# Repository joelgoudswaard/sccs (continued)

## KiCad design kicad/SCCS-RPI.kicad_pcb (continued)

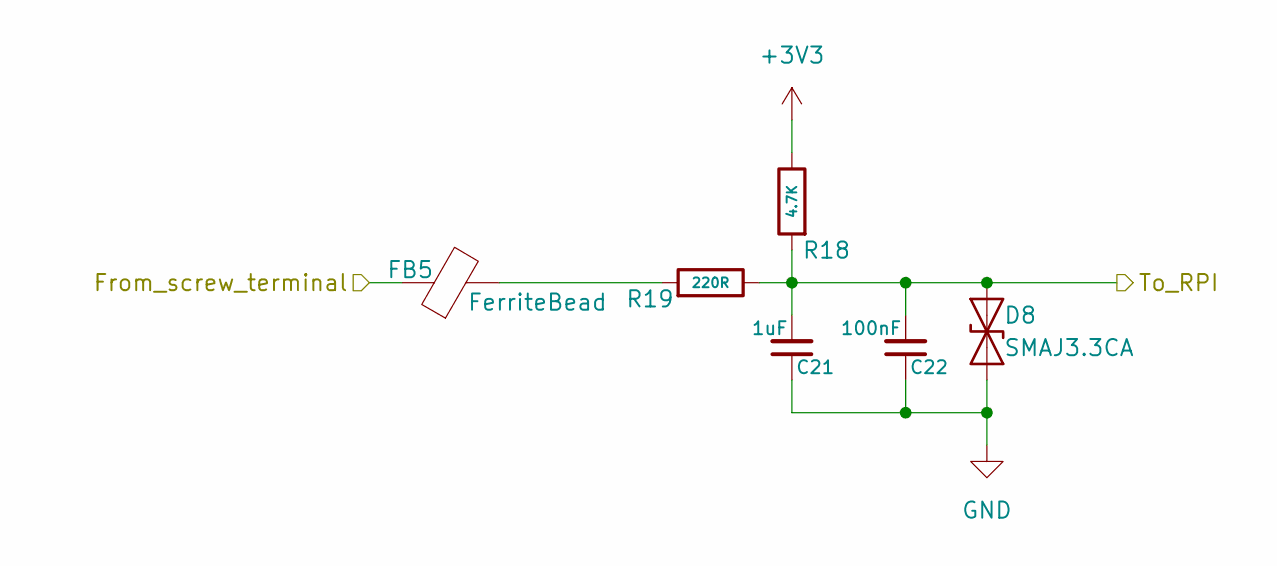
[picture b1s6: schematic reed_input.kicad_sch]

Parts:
C21: 1uF; C_0805_2012Metric; LCSC Part # C91185
C22: 100nF; C_0805_2012Metric; LCSC Part # C49678
D8: SMAJ3.3CA; D_SMA; LCSC Part # C18199545
FB5: FerriteBead; L_0603_1608Metric; LCSC Part # C1002
R18: 4.7K; R_0805_2012Metric; LCSC Part # C17673
R19: 220R; R_0805_2012Metric; LCSC Part # C17557

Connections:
+3V3: R18.1; also elsewhere on the board
/Reed1_input: C21.2, C22.2, D8.2 (A2), R18.2, R19.1; also elsewhere on the board
/Reed Switch 1/From_screw_terminal: FB5.1; also elsewhere on the board
GND: C21.1, C22.1, D8.1 (A1); also elsewhere on the board
unnamed: FB5.2, R19.2

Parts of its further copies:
C23, C25, C27, C29, C31, C33, C35: 1uF; C_0805_2012Metric; LCSC Part # C91185
C24, C26, C28, C30, C32, C34, C36: 100nF; C_0805_2012Metric; LCSC Part # C49678
D9, D10, D11, D12, D13, D14, D15: SMAJ3.3CA; D_SMA; LCSC Part # C18199545
FB6, FB7, FB8, FB9, FB10, FB11, FB12: FerriteBead; L_0603_1608Metric; LCSC Part # C1002
R20, R22, R24, R26, R28, R30, R32: 4.7K; R_0805_2012Metric; LCSC Part # C17673
R21, R23, R25, R27, R29, R31, R33: 220R; R_0805_2012Metric; LCSC Part # C17557

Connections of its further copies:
+3V3: R20.1, R22.1, R24.1, R26.1, R28.1, R30.1, R32.1; also elsewhere on the board
/Reed2_input: C23.2, C24.2, D9.2 (A2), R20.2, R21.1; also elsewhere on the board
/Reed3_input: C25.2, C26.2, D10.2 (A2), R22.2, R23.1; also elsewhere on the board
/Reed4_input: C27.2, C28.2, D11.2 (A2), R24.2, R25.1; also elsewhere on the board
/Reed5_input: C29.2, C30.2, D12.2 (A2), R26.2, R27.1; also elsewhere on the board
/Reed6_input: C31.2, C32.2, D13.2 (A2), R28.2, R29.1; also elsewhere on the board
/Reed7_input: C33.2, C34.2, D14.2 (A2), R30.2, R31.1; also elsewhere on the board
/Reed8_input: C35.2, C36.2, D15.2 (A2), R32.2, R33.1; also elsewhere on the board
/Reed Switch 2/From_screw_terminal: FB6.1; also elsewhere on the board
/Reed Switch 3/From_screw_terminal: FB7.1; also elsewhere on the board
/Reed Switch 4/From_screw_terminal: FB8.1; also elsewhere on the board
/Reed Switch 5/From_screw_terminal: FB9.1; also elsewhere on the board
/Reed Switch 6/From_screw_terminal: FB10.1; also elsewhere on the board
/Reed Switch 7/From_screw_terminal: FB11.1; also elsewhere on the board
/Reed Switch 8/From_screw_terminal: FB12.1; also elsewhere on the board
GND: C23.1, C24.1, C25.1, C26.1, C27.1, C28.1, C29.1, C30.1, C31.1, C32.1, C33.1, C34.1, C35.1, C36.1, D9.1 (A1), D10.1 (A1), D11.1 (A1), D12.1 (A1), D13.1 (A1), D14.1 (A1), D15.1 (A1); also elsewhere on the board
unnamed: FB6.2, R21.2
unnamed: FB7.2, R23.2
unnamed: FB8.2, R25.2
unnamed: FB9.2, R27.2
unnamed: FB10.2, R29.2
unnamed: FB11.2, R31.2
unnamed: FB12.2, R33.2

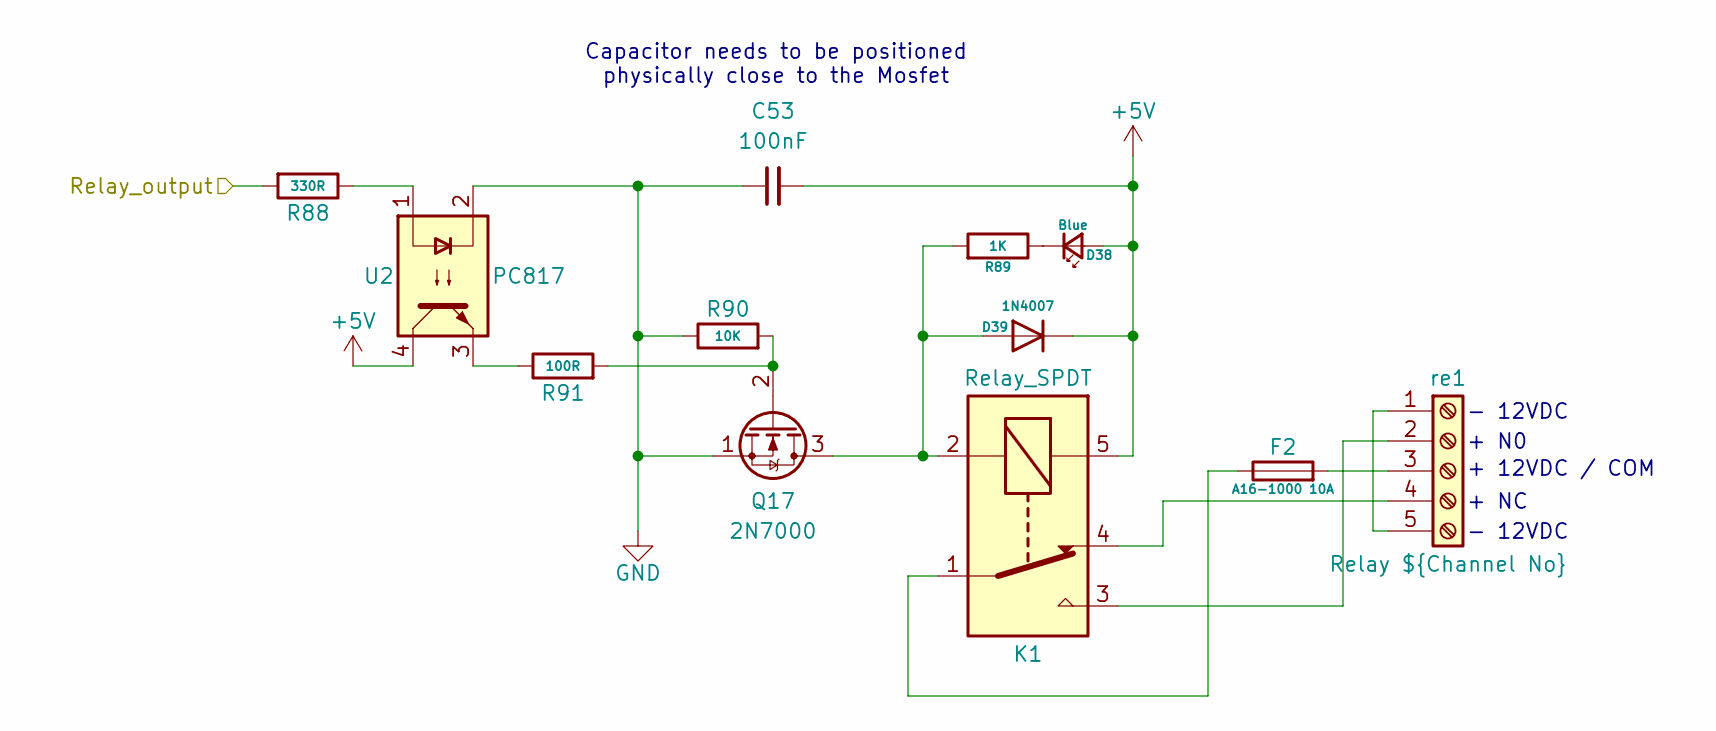
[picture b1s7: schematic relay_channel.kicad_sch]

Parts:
C53: 100nF; C_0805_2012Metric; LCSC Part # C49678
D38: Blue; LED_0603_1608Metric; LCSC Part # C2288
D39: 1N4007; D_SMA; LCSC Part # C64915
F2: A16-1000 10A; Fuse_Bourns_MF-RG1000; LCSC Part # C135398
K1: Relay_SPDT; Relay_SPDT_SANYOU_SRD_Series_Form_C; LCSC Part # C35449
Q17: 2N7000; TO-92_Inline; LCSC Part # C9114
R88: 330R; R_0805_2012Metric; LCSC Part # C17630
R89: 1K; R_0603_1608Metric; LCSC Part # C5123612
R90: 10K; R_0805_2012Metric; LCSC Part # C17414
R91: 100R; R_0805_2012Metric; LCSC Part # C17408
U2: PC817; DIP-4_W7.62mm; LCSC Part # C5353
re1: Relay ${Channel No}; TerminalBlock_Phoenix_MKDS-3-5-5.08_1x05_P5.08mm_Horizontal; LCSC Part # C8423

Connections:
+5V: C53.2, D38.2 (A), D39.1 (K), K1.5, U2.4; also elsewhere on the board
/Relay1_output: R88.2; also elsewhere on the board
GND: C53.1, Q17.1 (S), R90.1, U2.2; also elsewhere on the board
unnamed: D38.1 (K), R89.1
unnamed: D39.2 (A), K1.2, Q17.3 (D), R89.2
unnamed: F2.1, K1.1
unnamed: Q17.2 (G), R90.2, R91.2
unnamed: R88.1, U2.1
unnamed: R91.1, U2.3
unnamed: re1.1, re1.5
unnamed: K1.3, re1.2
unnamed: F2.2, re1.3
unnamed: K1.4, re1.4

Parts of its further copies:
C54, C55, C56: 100nF; C_0805_2012Metric; LCSC Part # C49678
D40, D42, D44: Blue; LED_0603_1608Metric; LCSC Part # C2288
D41, D43, D45: 1N4007; D_SMA; LCSC Part # C64915
F3, F4, F5: A16-1000 10A; Fuse_Bourns_MF-RG1000; LCSC Part # C135398
K2, K3, K4: Relay_SPDT; Relay_SPDT_SANYOU_SRD_Series_Form_C; LCSC Part # C35449
Q18, Q19, Q20: 2N7000; TO-92_Inline; LCSC Part # C9114
R92, R96, R100: 330R; R_0805_2012Metric; LCSC Part # C17630
R93, R97, R101: 1K; R_0603_1608Metric; LCSC Part # C5123612
R94, R98, R102: 10K; R_0805_2012Metric; LCSC Part # C17414
R95, R99, R103: 100R; R_0805_2012Metric; LCSC Part # C17408
U3, U4, U5: PC817; DIP-4_W7.62mm; LCSC Part # C5353

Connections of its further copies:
+5V: C54.2, C55.2, C56.2, D40.2 (A), D41.1 (K), D42.2 (A), D43.1 (K), D44.2 (A), D45.1 (K), K2.5, K3.5, K4.5, U3.4, U4.4, U5.4; also elsewhere on the board
/Relay2_output: R92.2; also elsewhere on the board
/Relay3_output: R96.2; also elsewhere on the board
/Relay4_output: R100.2; also elsewhere on the board
GND: C54.1, C55.1, C56.1, Q18.1 (S), Q19.1 (S), Q20.1 (S), R94.1, R98.1, R102.1, U3.2, U4.2, U5.2; also elsewhere on the board
unnamed: D40.1 (K), R93.1
unnamed: D41.2 (A), K2.2, Q18.3 (D), R93.2
unnamed: D42.1 (K), R97.1
unnamed: D43.2 (A), K3.2, Q19.3 (D), R97.2
unnamed: D44.1 (K), R101.1
unnamed: D45.2 (A), K4.2, Q20.3 (D), R101.2
unnamed: F3.1, K2.1
unnamed: F4.1, K3.1
unnamed: F5.1, K4.1
unnamed: Q18.2 (G), R94.2, R95.2
unnamed: Q19.2 (G), R98.2, R99.2
unnamed: Q20.2 (G), R102.2, R103.2
unnamed: R92.1, U3.1
unnamed: R95.1, U3.3
unnamed: R96.1, U4.1
unnamed: R99.1, U4.3
unnamed: R100.1, U5.1
unnamed: R103.1, U5.3
unnamed 189: K2.3; also elsewhere on the board
unnamed 190: F3.2; also elsewhere on the board
unnamed 191: K2.4; also elsewhere on the board
unnamed 193: K3.3; also elsewhere on the board
unnamed 194: F4.2; also elsewhere on the board
unnamed 195: K3.4; also elsewhere on the board
unnamed 197: K4.3; also elsewhere on the board
unnamed 198: F5.2; also elsewhere on the board
unnamed 199: K4.4; also elsewhere on the board

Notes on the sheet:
+ NC
+ N0
+ 12VDC / COM
- 12VDC
Capacitor needs to be positioned physically close to the Mosfet

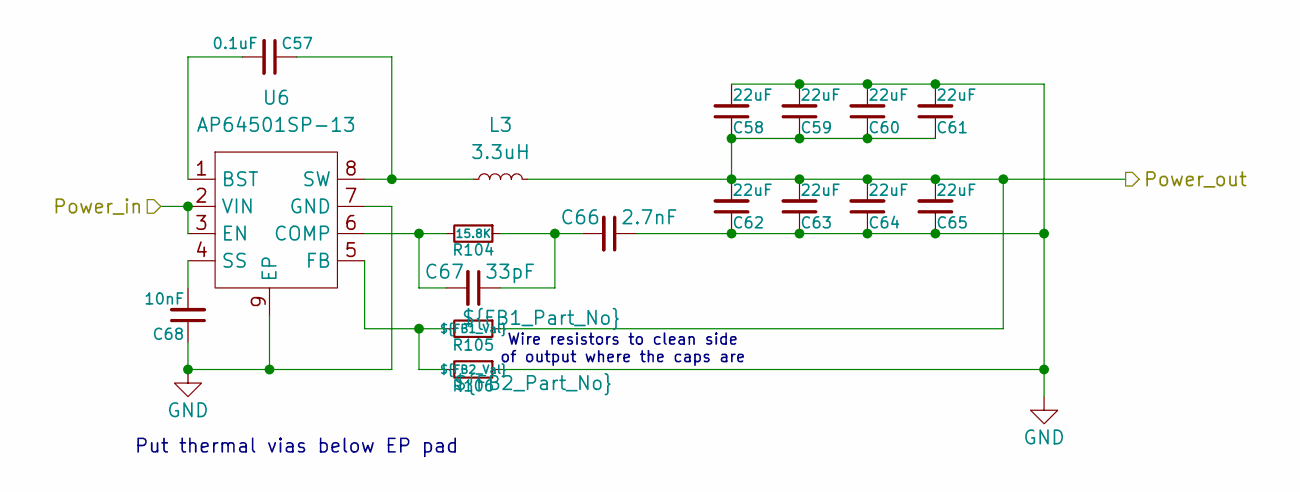
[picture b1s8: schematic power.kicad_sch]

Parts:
C57: 0.1uF; C_0805_2012Metric; LCSC Part # C86041
C58, C59, C60, C61, C62, C63, C64, C65: 22uF; C_0805_2012Metric; LCSC Part # C86816
C66: 2.7nF; C_0805_2012Metric; LCSC Part # C113859
C67: 33pF; C_0805_2012Metric; LCSC Part # C541516
C68: 10nF; C_0805_2012Metric; LCSC Part # C237168
L3: 3.3uH; L_SXN_SMDRI127; LCSC Part # C24550
R104: 15.8K; R_0805_2012Metric; LCSC Part # C17468
R105: ${FB1_Val}; R_0805_2012Metric; LCSC Part # ${FB1_Part_No}
R106: ${FB2_Val}; R_0805_2012Metric; LCSC Part # ${FB2_Part_No}
U6: AP64501SP-13; SOIC-8-1EP_3.9x4.9mm_P1.27mm_EP2.95x4.9mm_Mask2.71x3.4mm_Th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; LCSC Part # C2071517

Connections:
+5V: C58.1, C59.1, C60.1, C61.1, C62.2, C63.2, C64.2, C65.2, L3.2, R105.1; also elsewhere on the board
/Power - 3V3/Power_in: U6.2 (VIN), U6.3 (EN); also elsewhere on the board
GND: C58.2, C59.2, C60.2, C61.2, C62.1, C63.1, C64.1, C65.1, C66.1, C68.1, R106.1, U6.7 (GND), U6.9 (EP); also elsewhere on the board
unnamed: C66.2, C67.1, R104.1
unnamed: C57.2, U6.1 (BST)
unnamed: C67.2, R104.2, U6.6 (COMP)
unnamed: R105.2, R106.2, U6.5 (FB)
unnamed: C68.2, U6.4 (SS)
unnamed: C57.1, L3.1, U6.8 (SW)

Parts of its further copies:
C69: 0.1uF; C_0805_2012Metric; LCSC Part # C86041
C70, C71, C72, C73, C74, C75, C76, C77: 22uF; C_0805_2012Metric; LCSC Part # C86816
C78: 2.7nF; C_0805_2012Metric; LCSC Part # C113859
C79: 33pF; C_0805_2012Metric; LCSC Part # C541516
C80: 10nF; C_0805_2012Metric; LCSC Part # C237168
L4: 3.3uH; L_SXN_SMDRI127; LCSC Part # C24550
R107: 15.8K; R_0805_2012Metric; LCSC Part # C17468
U7: AP64501SP-13; SOIC-8-1EP_3.9x4.9mm_P1.27mm_EP2.95x4.9mm_Mask2.71x3.4mm_Th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; LCSC Part # C2071517

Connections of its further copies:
+3V3: C70.1, C71.1, C72.1, C73.1, C74.2, C75.2, C76.2, C77.2, L4.2; also elsewhere on the board
/Power - 3V3/Power_in: U7.2 (VIN), U7.3 (EN); also elsewhere on the board
GND: C70.2, C71.2, C72.2, C73.2, C74.1, C75.1, C76.1, C77.1, C78.1, C80.1, U7.7 (GND), U7.9 (EP); also elsewhere on the board
unnamed: C78.2, C79.1, R107.1
unnamed: C69.2, U7.1 (BST)
unnamed: C79.2, R107.2, U7.6 (COMP)
unnamed 177: U7.5 (FB); also elsewhere on the board
unnamed: C80.2, U7.4 (SS)
unnamed: C69.1, L4.1, U7.8 (SW)

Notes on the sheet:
Put thermal vias below EP pad
Wire resistors to clean side of output where the caps are

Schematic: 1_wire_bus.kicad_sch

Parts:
C17: 100nF; C_0805_2012Metric; LCSC Part # C49678
D7: SMAJ3.3CA; D_SMA; LCSC Part # C18199545
FB1: FerriteBead; L_0603_1608Metric; LCSC Part # C1002
R14: 2.2K; R_0805_2012Metric; LCSC Part # C17520
i3: Temp Sensors; TerminalBlock_Phoenix_MKDS-1,5-3-5.08_1x03_P5.08mm_Horizont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; LCSC Part # C8412

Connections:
+3V3: C17.1, R14.2, i3.1; also elsewhere on the board
/Temp1_sensor_input: D7.2 (A2), FB1.2, R14.1; also elsewhere on the board
GND: C17.2, D7.1 (A1), i3.3; also elsewhere on the board
unnamed: FB1.1, i3.2

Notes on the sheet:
Yellow/Data
Red/+
Black/-

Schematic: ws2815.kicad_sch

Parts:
D36: SMAJ5.0CA; D_SMA; LCSC Part # C78402
R86: 33R; R_0805_2012Metric; LCSC Part # C17634

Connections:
/WS281X Channel 1/WS281X_In: R86.1; also elsewhere on the board
/WS281X Channel 1/WS281X_Out: D36.2 (A2), R86.2; also elsewhere on the board
GND: D36.1 (A1); also elsewhere on the board

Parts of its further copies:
D37: SMAJ5.0CA; D_SMA; LCSC Part # C78402
R87: 33R; R_0805_2012Metric; LCSC Part # C17634

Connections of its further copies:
/WS281X Channel 2/WS281X_In: R87.1; also elsewhere on the board
/WS281X Channel 2/WS281X_Out: D37.2 (A2), R87.2; also elsewhere on the board
GND: D37.1 (A1); also elsewhere on the board

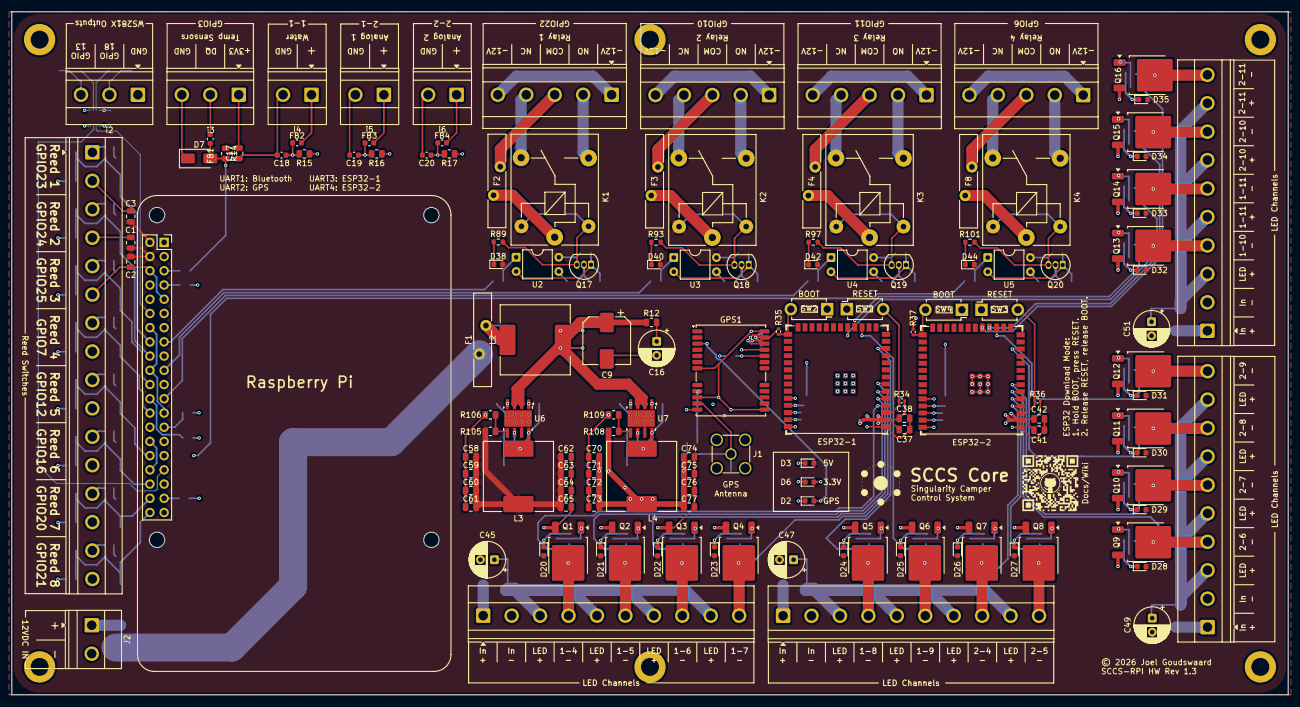
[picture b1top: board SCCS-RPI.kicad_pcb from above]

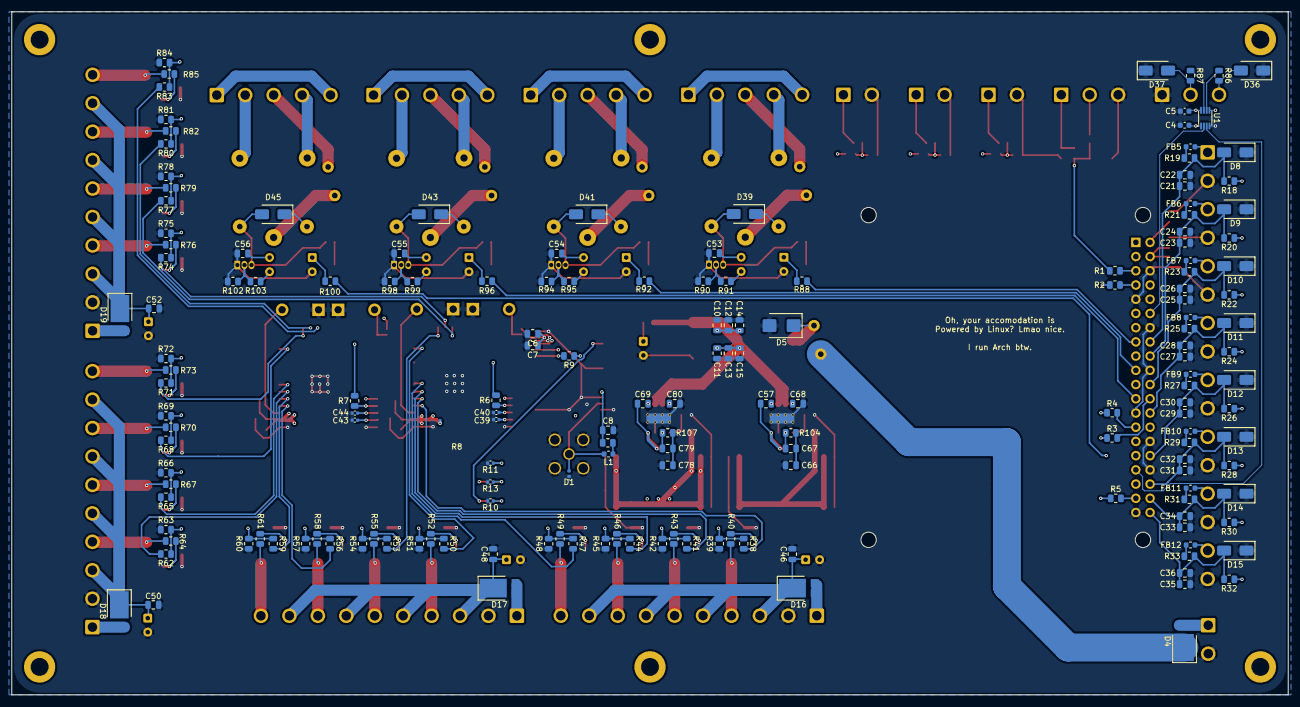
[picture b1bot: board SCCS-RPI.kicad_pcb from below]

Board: 4 copper layers, 228.0 x 122.0 mm, 311 parts (170 on the bottom side), 200 nets.

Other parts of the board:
D17, D18, D19: D_PowerDI-5
D21, D29: Red; LED_0603_1608Metric
D22, D30: Green; LED_0603_1608Metric
D23, D24, D25, D26, D27, D28, D31, D32, D33, D34, D35: White; LED_0603_1608Metric
R108: 100K; R_0805_2012Metric
R109: 32.4K; R_0805_2012Metric
RP?: Raspberry_Pi_2_3; raspberrypi_4
i5: Analog 1; TerminalBlock_Phoenix_MKDS-1,5-2-5.08_1x02_P5.08mm_Horizont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
i6: Analog 2; TerminalBlock_Phoenix_MKDS-1,5-2-5.08_1x02_P5.08mm_Horizont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
re2: Relay 2; TerminalBlock_Phoenix_MKDS-3-5-5.08_1x05_P5.08mm_Horizontal
re3: Relay 3; TerminalBlock_Phoenix_MKDS-3-5-5.08_1x05_P5.08mm_Horizontal
re4: Relay 4; TerminalBlock_Phoenix_MKDS-3-5-5.08_1x05_P5.08mm_Horizontal

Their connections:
+3V3: R108.1; also elsewhere on the board
+5V: D21.2 (A), D22.2 (A), D23.2 (A), D24.2 (A), D25.2 (A), D26.2 (A), D27.2 (A), D28.2 (A), D29.2 (A), D30.2 (A), D31.2 (A), D32.2 (A), D33.2 (A), D34.2 (A), D35.2 (A); also elsewhere on the board
/LED Power 2/12vdc_in: D17.2 (A); also elsewhere on the board
/LED Power 2/12vdc_out: D17.1 (K); also elsewhere on the board
/LED Power 3/12vdc_in: D18.2 (A); also elsewhere on the board
/LED Power 3/12vdc_out: D18.1 (K); also elsewhere on the board
/LED Power 4/12vdc_in: D19.2 (A); also elsewhere on the board
/LED Power 4/12vdc_out: D19.1 (K); also elsewhere on the board
GND: R109.1, i5.2, i6.2; also elsewhere on the board
unnamed 95: D21.1 (K); also elsewhere on the board
unnamed 96: D22.1 (K); also elsewhere on the board
unnamed 97: D23.1 (K); also elsewhere on the board
unnamed 98: D24.1 (K); also elsewhere on the board
unnamed 99: D25.1 (K); also elsewhere on the board
unnamed 100: D26.1 (K); also elsewhere on the board
unnamed 101: D27.1 (K); also elsewhere on the board
unnamed 102: D28.1 (K); also elsewhere on the board
unnamed 103: D29.1 (K); also elsewhere on the board
unnamed 104: D30.1 (K); also elsewhere on the board
unnamed 105: D31.1 (K); also elsewhere on the board
unnamed 106: D32.1 (K); also elsewhere on the board
unnamed 107: D33.1 (K); also elsewhere on the board
unnamed 108: D34.1 (K); also elsewhere on the board
unnamed 109: D35.1 (K); also elsewhere on the board
unnamed 177: R108.2, R109.2; also elsewhere on the board
unnamed 182: i5.1; also elsewhere on the board
unnamed 183: i6.1; also elsewhere on the board
unnamed: re2.1, re2.5
unnamed 189: re2.2; also elsewhere on the board
unnamed 190: re2.3; also elsewhere on the board
unnamed 191: re2.4; also elsewhere on the board
unnamed: re3.1, re3.5
unnamed 193: re3.2; also elsewhere on the board
unnamed 194: re3.3; also elsewhere on the board
unnamed 195: re3.4; also elsewhere on the board
unnamed: re4.1, re4.5
unnamed 197: re4.2; also elsewhere on the board
unnamed 198: re4.3; also elsewhere on the board
unnamed 199: re4.4; also elsewhere on the board

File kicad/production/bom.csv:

Designator,Footprint,Quantity,Value,LCSC Part #
"C1, C10",0805,2,10uF,C15850
"C11, C17, C2, C22, C24, C26, C28, C30, C32, C34, C36, C46, C48, C50, C52, C53, C54, C55, C56, C8",0805,20,100nF,C49678
"C12, C13, C14, C15, C3, C37, C41, C58, C59, C6, C60, C61, C62, C63, C64, C65, C70, C71, C72, C73, C74, C75, C76, C77",0805,24,22uF,C86816
"C16, C45, C47, C49, C51",CP_Radial_D6.3mm_P2.50mm,5,100uF,C44587
"C18, C19, C20, C4, C5",0603,5,100nF,C1590
"C21, C23, C25, C27, C29, C31, C33, C35",0805,8,1uF,C91185
"C38, C42, C57, C69, C7",0805,5,0.1uF,C86041
"C39, C40, C43, C44",0402,4,100nF,C60474
"C66, C78",0805,2,2.7nF,C113859
"C67, C79",0805,2,33pF,C541516
"C68, C80",0805,2,10nF,C237168
C9,CP_Elec_8x10,1,220uF,C165536
D1,0402,1,ESD103-B1-02EL,C535146
"D10, D11, D12, D13, D14, D15, D7, D8, D9",D_SMA,9,SMAJ3.3CA,C18199545
"D16, D17, D18, D19, D4",D_PowerDI-5,5,~,C2759901
D2,0603,1,GPS,C2286
"D20, D23, D24, D25, D26, D27, D28, D31, D32, D33, D34, D35",0603,12,White,C2290
"D21, D29",0603,2,Red,C2286
"D22, D30",0603,2,Green,C12065
D3,0603,1,5V,C2286
"D36, D37",D_SMA,2,SMAJ5.0CA,C78402
"D38, D40, D42, D44",0603,4,Blue,C2288
"D39, D41, D43, D45",D_SMA,4,1N4007,C64915
D5,D_SMB,1,SMAJ18A/TR13,C571369
D6,0603,1,3.3V,C2286
"ESP32-1, ESP32-2",ESP32-S3-WROOM-1U,2,ESP32-S3-WROOM-1,C3013946
"F1, F2, F3, F4, F5",Fuse_Bourns_MF-RG1000,5,A16-1000 10A,C135398
"FB1, FB10, FB11, FB12, FB2, FB3, FB4, FB5, FB6, FB7, FB8, FB9",0603,12,FerriteBead,C1002
GPS1,ublox_NEO,1,NEO-M9N-00B,C5119087
I1,"TerminalBlock_Phoenix_MKDS-1,5-16-5.08_1x16_P5.08mm_Horizontal",1,Reed Switches,C508906
I2,"TerminalBlock_Phoenix_MKDS-1,5-3-5.08_1x03_P5.08mm_Horizontal",1,WS281X Outputs,C8412
I3,"TerminalBlock_Phoenix_MKDS-1,5-3-5.08_1x03_P5.08mm_Horizontal",1,Temp Sensors,C8412
I4,"TerminalBlock_Phoenix_MKDS-1,5-2-5.08_1x02_P5.08mm_Horizontal",1,Water,C8445
I5,"TerminalBlock_Phoenix_MKDS-1,5-2-5.08_1x02_P5.08mm_Horizontal",1,Analog 1,C8445
I6,"TerminalBlock_Phoenix_MKDS-1,5-2-5.08_1x02_P5.08mm_Horizontal",1,Analog 2,C8445
J1,SMA_Amphenol_132134-11_Vertical,1,Conn_Coaxial,C20415804
J2,"TerminalBlock_Phoenix_MKDS-1,5-2-5.08_1x02_P5.08mm_Horizontal",1,12VDC IN,C8445
"K1, K2, K3, K4",Relay_SPDT_SANYOU_SRD_Series_Form_C,4,Relay_SPDT,C35449
L1,0603,1,27nH,C162550
"L2, L3, L4",L_SXN_SMDRI127,3,3.3uH,C24550
PI1,PinSocket_2x20_P2.54mm_Vertical,1,Raspberry PI HAT,C132132
"PWM1, PWM2, PWM3, PWM4","TerminalBlock_Phoenix_MKDS-1,5-10-5.08_1x10_P5.08mm_Horizontal",4,LED Channels,C29173
"Q1, Q10, Q11, Q12, Q13, Q14, Q15, Q16, Q2, Q3, Q4, Q5, Q6, Q7, Q8, Q9",TO-252-2,16,IRLR7843,C21988
"Q17, Q18, Q19, Q20",TO-92_Inline,4,2N7000,C9114
"R1, R19, R2, R21, R23, R25, R27, R29, R3, R31, R33, R4, R6, R7, R9",0805,15,220R,C17557
"R10, R11, R13",0402,3,1K,C11702
"R100, R88, R92, R96",0805,4,330R,C17630
"R101, R89, R93, R97",0603,4,1K,C5123612
"R102, R39, R42, R45, R48, R51, R54, R57, R60, R63, R66, R69, R72, R75, R78, R81, R84, R90, R94, R98",0805,20,10K,C17414
"R103, R38, R41, R44, R47, R50, R53, R56, R59, R62, R65, R68, R71, R74, R77, R80, R83, R91, R95, R99",0805,20,100R,C17408
"R104, R107",0805,2,15.8K,C17468
R105,0805,1,115K,C158272
R106,0805,1,22.1K,C17552
R108,0805,1,100K,C5123589
R109,0805,1,32.4K,C36938
R12,0805,1,1R,C25271
R14,0805,1,2.2K,C17520
"R15, R16, R17",0805,3,150R,C17471
"R18, R20, R22, R24, R26, R28, R30, R32, R5",0805,9,4.7K,C17673
"R34, R35, R36, R37",0402,4,10K,C60490
"R40, R43, R46, R49, R52, R55, R58, R61, R64, R67, R70, R73, R76, R79, R82, R85",0805,16,1K,C17513
R8,0805,1,10R,C17415
"R86, R87",0805,2,33R,C17634
RE1,TerminalBlock_Phoenix_MKDS-3-5-5.08_1x05_P5.08mm_Horizontal,1,Relay 1,C8423
RE2,TerminalBlock_Phoenix_MKDS-3-5-5.08_1x05_P5.08mm_Horizontal,1,Relay 2,C8423
RE3,TerminalBlock_Phoenix_MKDS-3-5-5.08_1x05_P5.08mm_Horizontal,1,Relay 3,C8423
RE4,TerminalBlock_Phoenix_MKDS-3-5-5.08_1x05_P5.08mm_Horizontal,1,Relay 4,C8423
RP?,raspberrypi_4,1,Raspberry_Pi_2_3,
"SW1, SW3",SW_PUSH_1P1T_6x3.5mm_H5.0_APEM_MJTP1250,2,RESET,C500070
"SW2, SW4",SW_PUSH_1P1T_6x3.5mm_H5.0_APEM_MJTP1250,2,BOOT,C500070
U1,VSSOP-8_2.3x2mm_P0.5mm,1,SN74LVC2T45DCUR,C15741
"U2, U3, U4, U5",DIP-4_W7.62mm,4,PC817,C5353
"U6, U7",SOIC-8-1EP_3.9x4.9mm_P1.27mm_EP2.95x4.9mm_Mask2.71x3.4mm_ThermalVias,2,AP64501SP-13,C2071517
